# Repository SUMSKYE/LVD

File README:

http://austindavid.com/t/lvd         # Overview page
http://austindavid.com/t/lvd-a       # Arduino-based version

The LVD is a microcontroller-drive Low Voltage Disconnect
system.

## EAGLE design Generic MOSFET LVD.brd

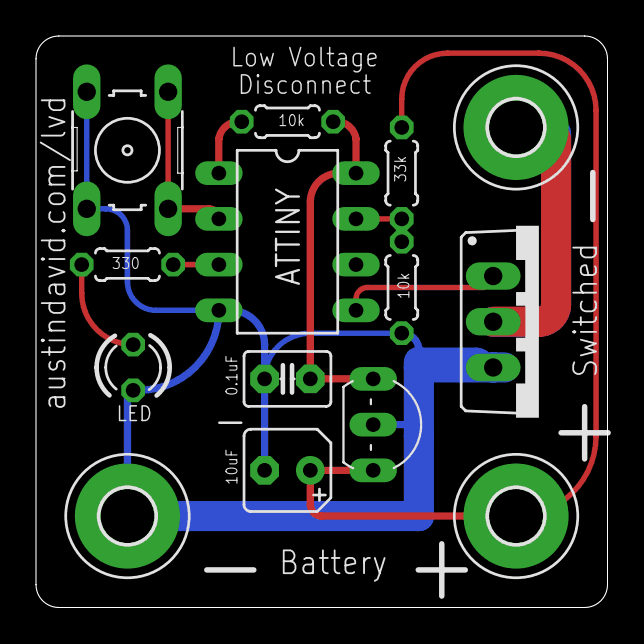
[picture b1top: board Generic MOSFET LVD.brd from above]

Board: 2 copper layers, 31.8 x 31.8 mm, 14 parts (0 on the bottom side), 10 nets.

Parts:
ATTINY: TINY13-20PU; DIL08
C1: 10uF; B45181A
C2: 0.1uF; C2.5-3
GND_BATT: MOUNT-PAD-ROUND3.0; 3,0-PAD
GND_SWITCHED: MOUNT-PAD-ROUND3.0; 3,0-PAD
LED: TLLR4400; LED3MM
Q1: IRF520; TO220BV
Q2: 2N5484; TO92-
R1, R4: 10k; 0204/5
R2: 330; 0204/5
R3: 33k; 0204/5
S1: B3F-10XX
V_BATT: MOUNT-PAD-ROUND3.0; 3,0-PAD

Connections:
BUTTON: ATTINY.2, S1.1, S1.2
GND: ATTINY.4, C1.-, C2.2, GND_BATT.B3,0, LED.K, Q1.S, Q2.2, R4.1, S1.3, S1.4
GND_SWITCHED: GND_SWITCHED.B3,0, Q1.D
LED: ATTINY.3, R2.1
unnamed: ATTINY.1, R1.2
unnamed: LED.A, R2.2
RELAY: ATTINY.5, Q1.G
VCC: ATTINY.8, C2.1, Q2.3, R1.1
V_BATT: C1.+, Q2.1, R3.1, V_BATT.B3,0
V_SENSE: ATTINY.7, R3.2, R4.2

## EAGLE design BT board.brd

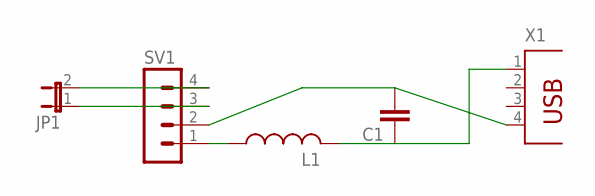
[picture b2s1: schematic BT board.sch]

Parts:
C1: C5/2.5; C5B2.5
JP1: JP1E; JP1
L1: L-US0204V; 0204V
SV1: MA04-1
X1: PN87520

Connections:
unnamed: L1.1, SV1.1
unnamed: C1.1, L1.2, X1.1
unnamed: C1.2, SV1.2, X1.4
unnamed: JP1.2, SV1.4
unnamed: JP1.1, SV1.3

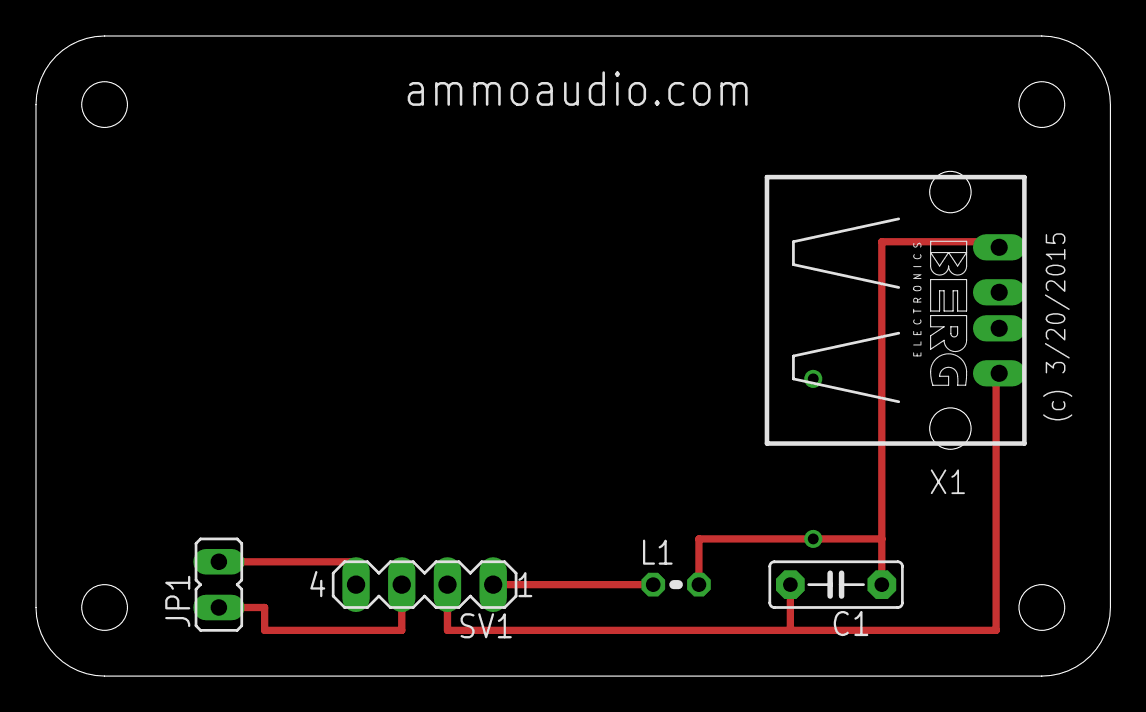
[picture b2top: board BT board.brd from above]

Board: 2 copper layers, 59.7 x 35.6 mm, 5 parts (0 on the bottom side), 5 nets.

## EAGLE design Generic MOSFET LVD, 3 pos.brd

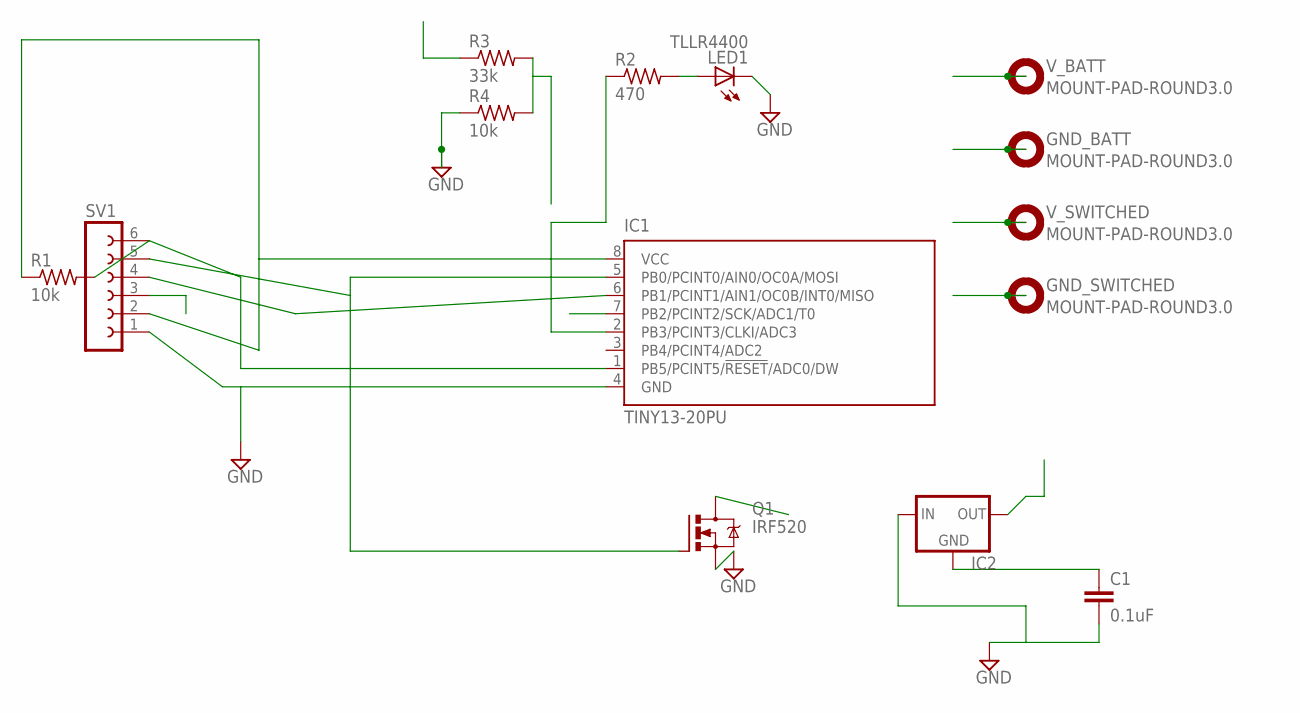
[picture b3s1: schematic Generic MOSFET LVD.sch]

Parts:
C1: 0.1uF; C2.5-3
GND_BATT: MOUNT-PAD-ROUND3.0; 3,0-PAD
GND_SWITCHED: MOUNT-PAD-ROUND3.0; 3,0-PAD
IC1: TINY13-20PU; DIL08
IC2: 78XXS
LED1: TLLR4400; LED3MM
Q1: IRF520; TO220BV
R1, R4: 10k; 0204/5
R2: 470; 0204/5
R3: 33k; 0204/5
SV1: FE06-1; FE06
V_BATT: MOUNT-PAD-ROUND3.0; 3,0-PAD
V_SWITCHED: MOUNT-PAD-ROUND3.0; 3,0-PAD

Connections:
GND: C1.2, GND_BATT.B3,0, IC1.4 (GND), IC2.IN, LED1.K (C), Q1.S, R4.1, SV1.1
GND_SWITCHED: GND_SWITCHED.B3,0, Q1.D
LED_SIGNAL: IC1.2 (PB3/PCINT3/CLKI/ADC3), R2.1
unnamed: IC1.1 (PB5/PCINT5/!RESET!/ADC0/DW), R1.2, SV1.6
unnamed: LED1.A, R2.2
unnamed: IC1.5 (PB0/PCINT0/AIN0/OC0A/MOSI), Q1.G, SV1.5
unnamed: IC1.6 (PB1/PCINT1/AIN1/OC0B/INT0/MISO), SV1.4
VCC: C1.1, IC1.8 (VCC), IC2.GND, R1.1, SV1.2
V_BATT: IC2.OUT, R3.1, V_BATT.B3,0, V_SWITCHED.B3,0
V_SENSE: IC1.7 (PB2/PCINT2/SCK/ADC1/T0), R3.2, R4.2, SV1.3

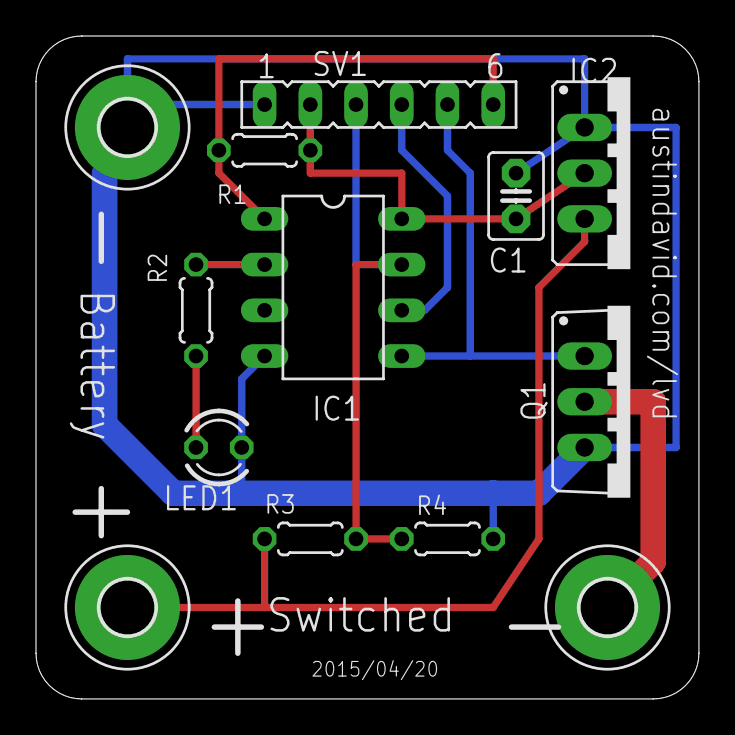
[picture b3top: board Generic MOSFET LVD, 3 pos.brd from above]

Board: 2 copper layers, 36.8 x 36.8 mm, 13 parts (0 on the bottom side), 10 nets.

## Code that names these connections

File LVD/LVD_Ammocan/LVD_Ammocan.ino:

/*
 * A "flashy" LVD circuit: http://austindavid/lvd
 * Austin David, austin@austindavid.com 6 Sept 2013
 * (cc)
 */

/*
 * The ADC is fed wth a voltage divider, 10k + 49.9k
 * Ideal voltage conversion:
 * ADC = Vin * (10 / (10 + 49.9)) / 5 * 1024
 * 
 * 11.3v -> ADC @ 387
 * 10.5v -> ADC @ 359
 * 
 * YMMV :)  These values are pretty wrong on a breadboard (lots of weird
 * resistances), but work great on a tight soldered protoboard.
 *
 * Make one, ground the debug pin, and check the values; reprogram if needed.
 *
 *
 * For the new PCB LVD, 10k + 33k @ 3.3v VCC
 *   ADC = Vin * (10/(10+33)) / 3.3 * 1024
 * 11.5 -> 902
 * 11.0 -> 794
 *
 *  at 5V, 47.62/V
 *  12.0 -> 571.44
 *  11.5 -> 547.63
 *  11.0 -> 523.82
 *
 *
 * bench observed:
 *   12.0 =~ 547
 */
 
/* experimental 
#define HIGH_WATER 550 
#define LOW_WATER 530
*/

#define VOLTAGE_SCALE        47.62
#define VOLTAGE_CALIBRATION  (13.1 * VOLTAGE_SCALE)
#define VOLTAGE_HIGH         (12.0 * VOLTAGE_SCALE)
#define VOLTAGE_LOW          (11.5 * VOLTAGE_SCALE)

/*
 * ATTiny45 don't have hardware serial (or, I don't use it) and have
 * different pin layouts from a typical Uno dev board
 */

#ifdef __AVR_ATtiny45__
#define ATTINY
#endif

#ifdef __AVR_ATtiny85__
#define ATTINY
#endif

// ATMEL ATTINY45 / ARDUINO
//
//                  +-\/-+
// Ain0 (D 5) PB5  1|    |8  Vcc
// Ain3 (D 3) PB3  2|    |7  PB2 (D 2) Ain1
// Ain2 (D 4) PB4  3|    |6  PB1 (D 1) pwm1
//            GND  4|    |5  PB0 (D 0) pwm0
//                  +----+


#define JUMPER  A0 // DIP 1, also RESET so be careful
#define V_SENSE A1 // DIP 7
#define RED      3 // DIP 2
#define RELAY 0    // DIP 5

#ifndef ATTINY     // Arduino UNO or other board
#define RELAY 13   // the built-in LED on an Uno
#endif 


byte state;

#define NUMBER_OF_SAMPLES 20
#define DELAY_BETWEEN_SAMPLES 10 // ms
int sampleVoltage(byte pin) {
  int voltage, sum;
  sum = 0;
  for (int i = 0; i < NUMBER_OF_SAMPLES; i++) {
    sum += analogRead(pin);
    delay(DELAY_BETWEEN_SAMPLES);
  }
  voltage = sum / NUMBER_OF_SAMPLES;
  return voltage;
}


void flash(byte pin, byte nr_flashes) {
  for (byte i = 0; i < nr_flashes; i++) {
    digitalWrite(pin, HIGH);
    delay(100);
    digitalWrite(pin, LOW);
    delay(100);
  }  
} // flash(pin, nr_flashes)


void try_to_calibrate(void) {
  int jumperValue, sum;
  
  sum = 0;
  for (byte i = 0; i < 10; i++) {
    sum += analogRead(JUMPER);
    delay(5);
  }
  
  jumperValue = sum / 10;
  
  if (jumperValue < 750) {
    flash(RED, 5); 
    int calibrated_voltage = sampleVoltage(V_SENSE);
    
   }
  
} // try_to_calibrate()


void read_calibration(void) {
  delay(500);
  flash(RED, 2);
  delay(500);
  flash(RED, 2);
} // read_calibration()


void setLVD(byte level) {
  state = level;
  digitalWrite(RED, !level);
  digitalWrite(RELAY, level);
}


// the setup routine runs once when you press reset:
void setup() {
  #ifndef ATTINY
  // initialize serial communication at 9600 bits per second:
  Serial.begin(9600);
  #endif 
  pinMode(V_SENSE, INPUT);
  pinMode(RELAY, OUTPUT);
  pinMode(RED, OUTPUT);
  
  // default state: off + quiet
  state = LOW;
  digitalWrite(RELAY, LOW);
  digitalWrite(RED, LOW);
  
  // check to see if we're supposed to recalibrate
  try_to_calibrate();
  
  // read a calibrated value for the ADC
  read_calibration();
  
  // try to set it "on" *once*
  int voltage = sampleVoltage(V_SENSE);
  if (voltage > HIGH_WATER) {
    setLVD(HIGH);
  } else {
    setLVD(LOW);
  }
} // setup()


// the loop routine runs over and over again forever:
void loop() {
  int voltage = sampleVoltage(V_SENSE);
  
#ifndef ATTINY
  // print out the value you read:
  Serial.println(voltage);
#endif

  if (voltage < LOW_WATER) {
    setLVD(LOW);
    delay(999999); // sleep a long time
  }
   
  delay(100); 
} // loop()

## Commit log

2014-05-09 adding README
2014-05-09 PICAXE code for LVD (final)
    This is the final, deployed / running code for the LVD
2014-05-09 Arduino-based LVD
    final code released to BioQuip
2015-12-28 updating with the last ~ 2y LVD work
    adds new boards for the ATtiny45/85-based PCB, the code used in the
    Ammocan, and some alternate builds
2015-12-28 custom ~13V cutoff
    setting HIGH_WATER / LOW_WATER around 13V for an automotive application
2016-04-01 new "Calibrating" LVD code
    similar to the ammocan revision, but self-recovering.
2016-05-16 New "touchy" pushbutton code
    This is for a new LVD which uses a button to set / calibrate levels, or
    to toggle state(s)
2016-05-16 new 4/10 LVD
    Smaller, with a built-in pushbutton. Dropped the 6-pin debugging
    header.
